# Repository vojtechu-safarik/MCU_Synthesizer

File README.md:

# Polyphonic Synthesizer for Teensy 4.1 

### Abstract
This project is an advanced realization of bachelor's project at Brno Univesity of Technology. 
It creates a digital synthesizer using a microcontroller development board, encompassing code development and a prototype build (including PCBs).
The C++ code has been made in VS Code using PlatformIO and it utilises Teensy Audio Library. 
The scripts that generate wavetables (as a header file) have been made using Python.
Those header files have been further edited in order to lower the amount of anti-aliasing using a MATLAB script. 

[**Video demonstration of the Synthesizer**](https://youtu.be/89R-V2SBuqk)

## Synthesis controls

### Oscillators
The synthesizer features both Poly and Unison voice allocation modes. Sound generation relies on wavetables categorized into 6 distinct families: Saw, Square (featuring Pulse Width Modulation), Triangle, Sine, Instrument, and Voice. Users can select the waveform type using the `Wave` control and seamlessly interpolate between variations using the `Shape` parameter. In Poly mode, each note gets its own independent audio chain, while Unison mode stacks three parallel oscillators per note for a thicker sound. Additionally, a sub-oscillator can be introduced, transposing the primary frequency one or two octaves down.

### Filters
The signal chain utilizes two main filters. The primary is a 24 dB/oct resonant Low-Pass Filter based on the Huovilainen New Moog mathematical model, which is capable of self-oscillation. This is followed in series by a 12 dB/oct High-Pass Filter based on the State Variable Filter model. The Low-Pass Filter also includes a dedicated Keyboard Tracking feature, allowing the cutoff frequency to scale dynamically with the pitch of the note played.

### Envelopes
Each voice is equipped with two dedicated ADSR (Attack, Decay, Sustain, Release) envelopes, allowing stages up to 3 seconds in length. One envelope shapes the final amplitude of the signal, while the other modulates the Low-Pass Filter's cutoff frequency. The filter envelope also features an `Intensity` control, enabling users to finely scale or invert the depth of the modulation.

### LFO
The Low-Frequency Oscillator can modulate the LPF Cutoff, Oscillator Shape, and Voice Pitch (Detune). It features four operational modes: `Free` (a single global LFO for all voices), `Retrig` (independent LFO per voice), and `Rise` or `Fall` (one-shot linear modulations triggered per note). Available waveforms include Sine, Saw Rise, Saw Fall, Square, and a randomized Noise sample. Users can adjust the modulation `Rate` (0.1–25 Hz), `Depth`, and a fade-in `Delay` of up to 3 seconds.

### Portamento
Available exclusively in Unison mode, Portamento introduces a smooth glide between overlapping notes. Its speed is synchronized to the global BPM and can be operated in two modes: `Time`, where the glide duration is a fixed note division regardless of the pitch distance, and `Rate`, where the glide duration scales with the interval, defined by the time it takes to travel one octave.

### Sequencer
A built-in step sequencer synchronizes to the global BPM and features two main performance modes. `Arp` mode functions as a traditional arpeggiator playing held notes in sequence, whereas `Latch` mode captures pressed keys into a buffer and plays them continuously without requiring the keys to be held. The sequence playback can be customized with order settings (Up, Down, As Played), octave duplications (+1 or +2 octaves), and an adjustable `Gate` parameter defining the note length (1–100%) per step. There's also an option to adjust the each individual step length via secret settings.

### Drone
This alternative ambient mode leverages 10 additional parallel oscillator chains utilizing simplified SVF filters, split into two alternating groups (A and B), alongside independent noise generators. Using the `Save` mode, users can capture the exact parameter settings of currently active voices and store them to one of 8 dedicated buttons. Switching to `Hold` mode allows users to endlessly play back these captured static drones concurrently with the standard synthesis engine.

## List of hardware components

* Teensy 4.1 Development board

* Audio Adaptor Board for Teensy (Rev D)

* 16-Channel Analog/Digital Multiplexer/Demultiplexer, CD74HC4067
  - used for various parameter configuration via potentiometers and toggle switches
  - 3 modules used in total 

  ### Mux 1 Channels:
  | Mux Channel | Parameter name | Connected Component |
  | :--- | :--- | :--- |
  | C0 | **Wave 1** | **Potentiometer** |
  | C1 | **Wave 2** | **Potentiometer** |
  | C2 | **Wave 3** | **Potentiometer** |
  | C3 | **Shape 1** | **Potentiometer** |
  | C4 | **Shape 2** | **Potentiometer** |
  | C5 | **Shape 3** | **Potentiometer** |
  | C6 | **Volume 1** | **Potentiometer** |
  | C7 | **Volume 2** | **Potentiometer** |
  | C8 | **Volume 3** | **Potentiometer** |
  | C9 | **Tune 1** | **Potentiometer** |
  | C10 | **Tune 2** | **Potentiometer** |
  | C11 | **Tune 3** | **Potentiometer** |
  | C12 | **Pink Noise** | **Potentiometer** |
  | C13 | **SynthMode - Poly** | **2-way Toggle Switch** |
  | C14 | **Sub-OSC - OFF** | **3-way Toggle Switch** |
  | C15 | **Sub-OSC - +2 octaves** | **3-way Toggle Switch** |

  ### Mux 2 Channels:
  | Mux Channel | Parameter name | Connected Component |
  | :--- | :--- | :--- |
  | C0 | **LPF Cutoff** | **Potentiometer** |
  | C1 | **LPF Resonance** | **Potentiometer** |
  | C2 | **Keyboard Tracking** | **Potentiometer** |
  | C3 | **Filter Envelope Intensity** | **Potentiometer** |
  | C4 | **HPF Cutoff** | **Potentiometer** |
  | C5 | **Filter Attack** | **Potentiometer** |
  | C6 | **Filter Decay** | **Potentiometer** |
  | C7 | **Filter Sustain** | **Potentiometer** |
  | C8 | **Filter Release** | **Potentiometer** |
  | C9 | **LFO Rate** | **Potentiometer** |
  | C10 | **LFO Depth** | **Potentiometer** |
  | C11 | **LFO Delay** | **Potentiometer** |
  | C12 | **Amplitude Attack** | **Potentiometer** |
  | C13 | **Amplitude Decay** | **Potentiometer** |
  | C14 | **Amplitude Sustain** | **Potentiometer** |
  | C15 | **Amplitude Release** | **Potentiometer** |

  ### Mux 3 Channels:
  | Mux Channel | Parameter name | Connected Component |
  | :--- | :--- | :--- |
  | C0 | **Master Volume** | **Potentiometer** |
  | C1 | **Sequencer Gate** | **Potentiometer** |
  | C2 | **LFO Type - Frequency** | **3-way Toggle Switch** |
  | C3 | **LFO Type - Tune** | **3-way Toggle Switch** |
  | C4 | **Portamento - ON** | **2-way Toggle Switch** |
  | C5 | **Portamento - Mode** | **2-way Toggle Switch** |
  | C6 | **Drone - mode** | **2-way Toggle Switch** |
  | C7 | **Sequencer Mode - OFF** | **3-way Toggle Switch** |
  | C8 | **Sequencer Mode - Latch** | **3-way Toggle Switch** |
  | C9 | **Sequencer Order - Up** | **3-way Toggle Switch** |
  | C10 | **Sequencer Order - Queue** | **3-way Toggle Switch** |
  | C11 | **Sequencer Octaves - 0** | **3-way Toggle Switch** |
  | C12 | **Sequencer Octaves - 2** | **3-way Toggle Switch** |

* 8-bit I/O Expander I2C-Bus, PCF8574T
  - used for LED signals for parameter state identification 
  - 2 modules used in total 

  ### I/O Expander 1 Pinout:
  | I/O Expander Pin | Parameter name |
  | :--- | :--- |
  | P0 | **LFO Mode #1** |
  | P1 | **LFO Mode #2** |
  | P2 | **LFO Mode #3** |
  | P3 | **LFO Mode #4** |
  | P4 | **LFO Wave #1** |
  | P5 | **LFO Wave #2** |
  | P6 | **LFO Wave #3** |
  | P7 | **LFO Wave #4** |

  ### I/O Expander 2 Pinout:
  | I/O Expander Pin | Parameter name |
  | :--- | :--- |
  | P0 | **Sequencer Rate #3** |
  | P1 | **Sequencer Rate #4** |
  | P2 | **LFO Wave #5** |
  | P3 | **Portamento Rate #1** |
  | P4 | **Portamento Rate #2** |
  | P5 | **Portamento Rate #3** |
  | P6 | **Portamento Rate #4** |
  | P7 | **Portamento Rate #5** |

* 3.2" 240x320 TFT display, ILI9341
  - SPI Display used for wavetable state reading

* Potentiometers
  - 20 Rotary B5K (WH148)
  - 11 Slider B10K (60mm)

* Rotary Encoder, KY-040
  - used for BPM configuration
  - button is used for preset selection

* Keyboard switches, MX linear Red
  - set up as a matrix to preserve pins

* Toggle switches
- 3× KN3 2-way toggle switch
- 2× KN3 3-way toggle switch
- 1× MTS-102 2-way toggle switch
- 3× MTS-103 3-way toggle switch

* Basic electronic components
- Resistors
  - 1× 100 (for Display backlight)
  - 22× 1k (for LEDs)
  - 14× 10k (pull resistors)
- Capacitors
  - 5× Ceramic 100nF (for coupling)
- Diodes
  - 43× 1N4148 (for Keyboard switches)
- LEDs
  - 22× 3mm Red
- Terminal blocks
  - 45× 3-Pin 2.54mm
  - 6× 2-Pin 2.54mm

## Circuit & PCB schematics

Circuit & PCB schematics have been made in KiCad 9.0 and the project is available [here.](./Design/KiCad)

## Pinout Configuration

| Teensy Pin | Pin name | Connected Components |
| :--- | :--- | :--- |
| 0 | **SW** | **Rotary Encoder** |
| 1 | **DT** | **Rotary Encoder** |
| 2 | **CLK** | **Rotary Encoder** |
| 3 | **S0** | **Mux #1, #2 and #3** |
| 4 | **S1** | **Mux #1, #2 and #3** |
| 5 | **S2** | **Mux #1, #2 and #3** |
| 6 | **S3** | **Mux #1, #2 and #3** |
| 7 | **DIN** | **Audioshield** |
| 8 | **DOUT** | **Audioshield** |
| 9 | **D/C** | **Display** |
| 10 | **CS** | **Display** |
| 11 | **SDI (MOSI)** | **Display** |
| 12 | **SDO (MISO)** | **Display** |
| 13 | **SCK** | **Display** |
| 14 | **Signal #1** | **LED #1 (Sequencer Rate #1)** |
| 15 | **Signal #2** | **LED #2 (Octave #4)** |
| 16 | **Signal #3** | **LED #3 (Octave #3)** |
| 17 | **Signal #4** | **LED #4 (Octave #2)** |
| 18 | **SDA** | **Audioshield** |
| 19 | **SCL** | **Audioshield** |
| 20 | **LRCLK** | **Audioshield** |
| 21 | **BCLK** | **Audioshield** |
| 22 | **Signal #5** | **LED #5 (Octave #1)** |
| 23 | **MCLK** | **Audioshield** |
| 24 | **Row #1** | **Keyboard** |
| 25 | **Row #2** | **Keyboard** |
| 26 | **Row #3** | **Keyboard** |
| 27 | **Row #4** | **Keyboard** |
| 28 | **Row #5** | **Keyboard** |
| 29 | **Row #6** | **Keyboard** |
| 30 | **Row #7** | **Keyboard** |
| 31 | **Row #8** | **Keyboard** |
| 32 | **Row #9** | **Keyboard** |
| 33 | **Column #1** | **Keyboard** |
| 34 | **Column #2** | **Keyboard** |
| 35 | **Column #3** | **Keyboard** |
| 36 | **Column #4** | **Keyboard** |
| 37 | **Column #5** | **Keyboard** |
| 38 | **Signal #6** | **LED #6 (Sequencer Rate #2)** |
| 39 | **Sig (A15)** | **Mux #1** |
| 40 | **Sig (A16)** | **Mux #2** |
| 41 | **Sig (A17)** | **Mux #3** |

### Images

### 3D Model

The 3D model has been made for laser engraving of the control panel. 

### Possible improvements

* The Line Out connector doesn't work now, and I don't know why, but I suppose it's not of mechanical nature.
* The GND is pretty noisy as of now, especially when powering via USB.
* Preset function isn't developed yet, but will be once I return to this project later.

## References

* Teensy 4.1 information: [link PJRC.com](https://www.pjrc.com/store/teensy41.html)
* Audio Adaptor Board for Teensy information: [link PJRC.com](https://www.pjrc.com/store/teensy3_audio.html)
* Incredible source of information and amazing YouTube content: [link notesandvolts.com](https://www.notesandvolts.com)
* I hereby acknowledge use of free-license AI tool for coding: [link gemini.google.com](https://gemini.google.com)

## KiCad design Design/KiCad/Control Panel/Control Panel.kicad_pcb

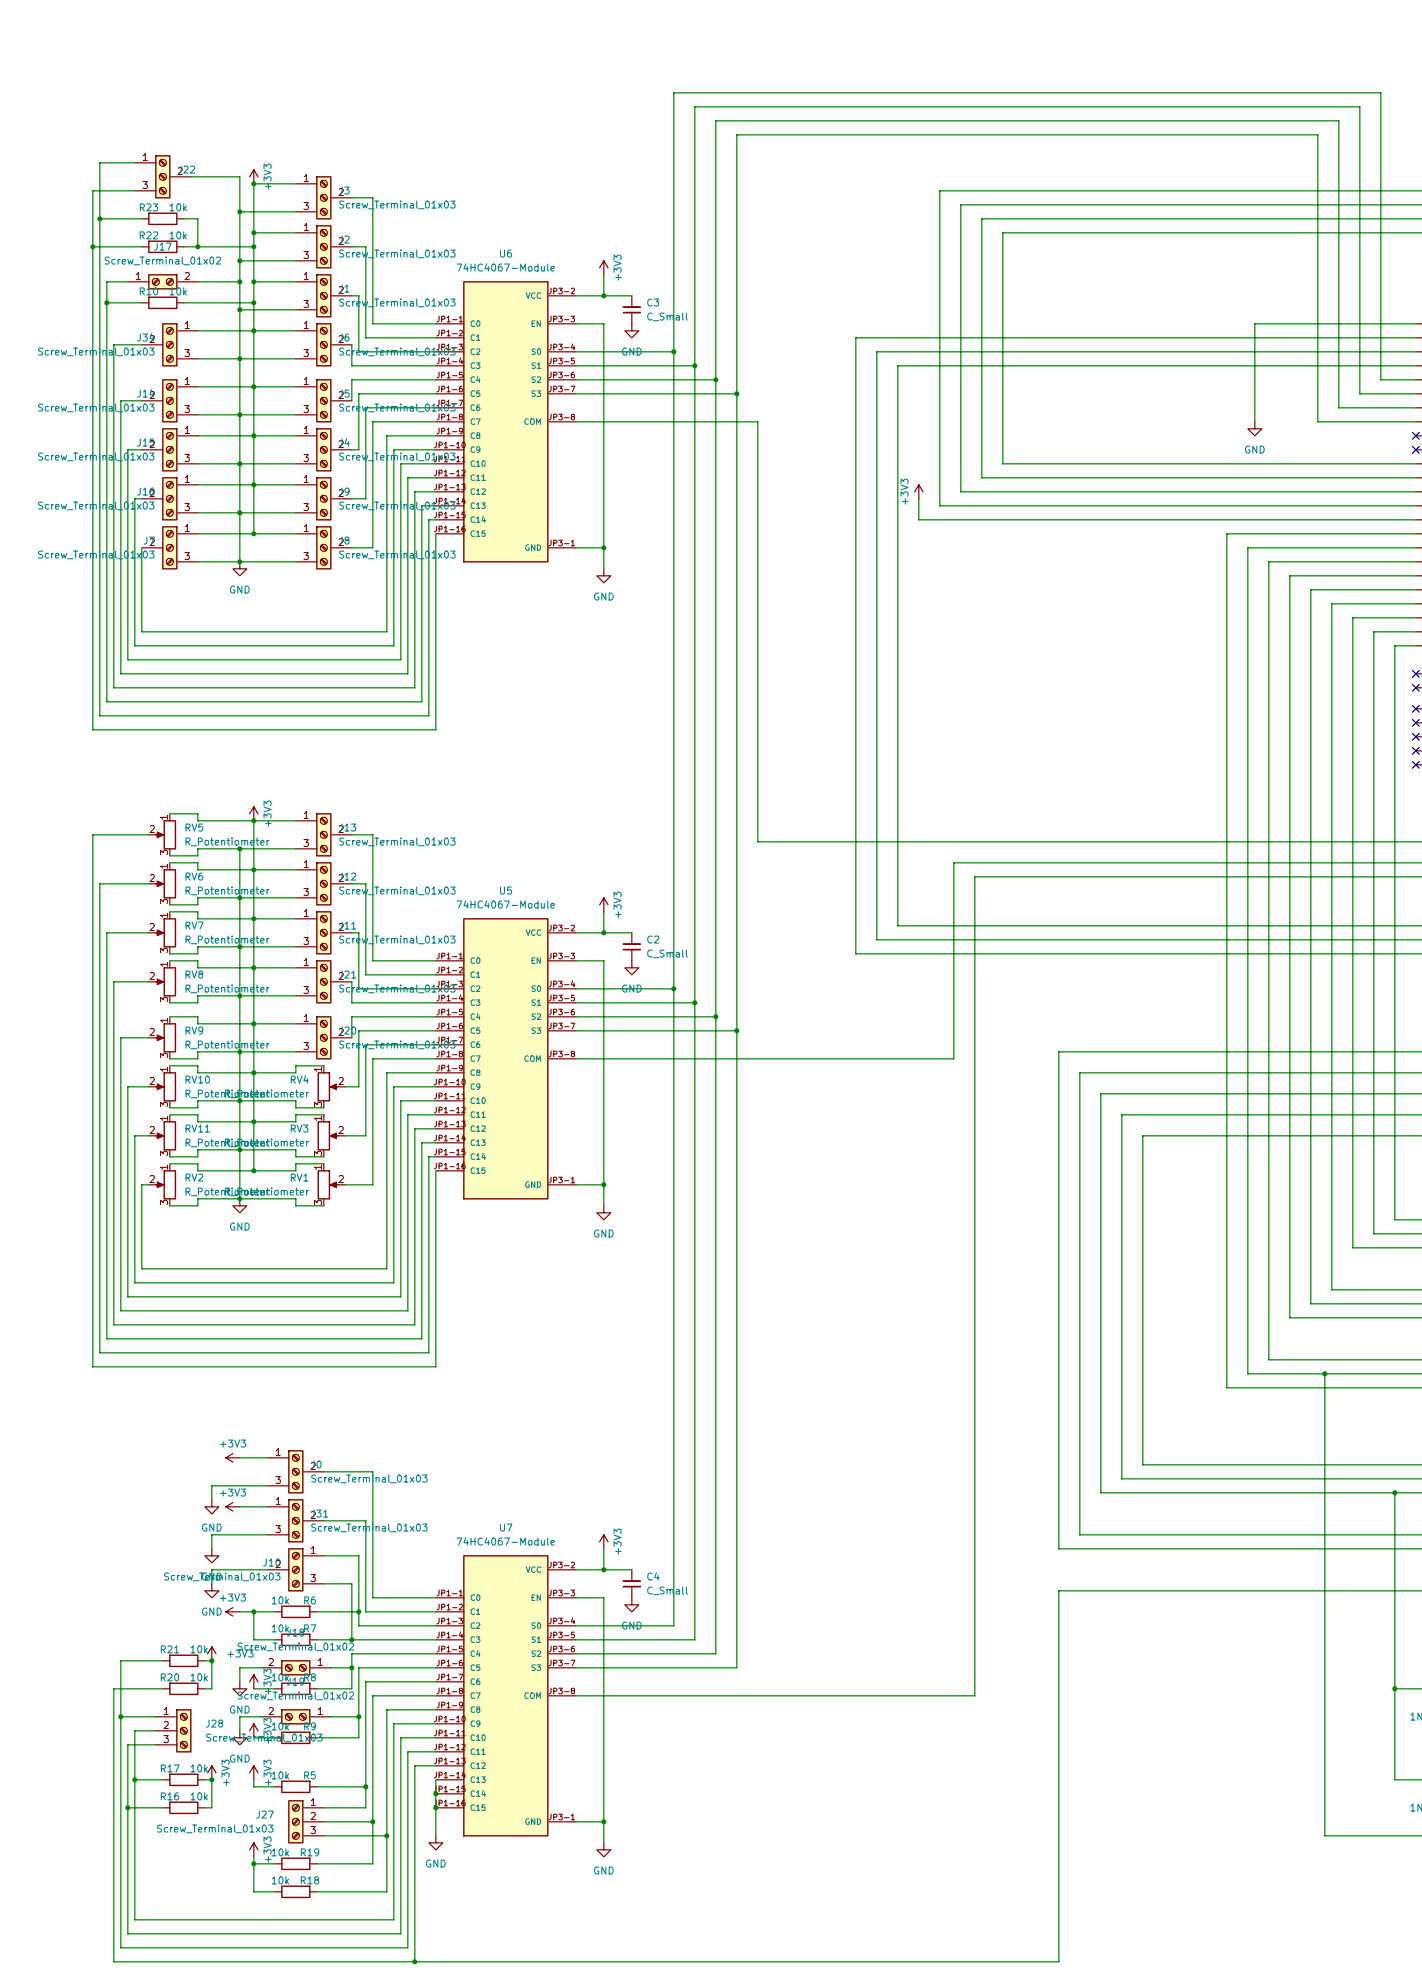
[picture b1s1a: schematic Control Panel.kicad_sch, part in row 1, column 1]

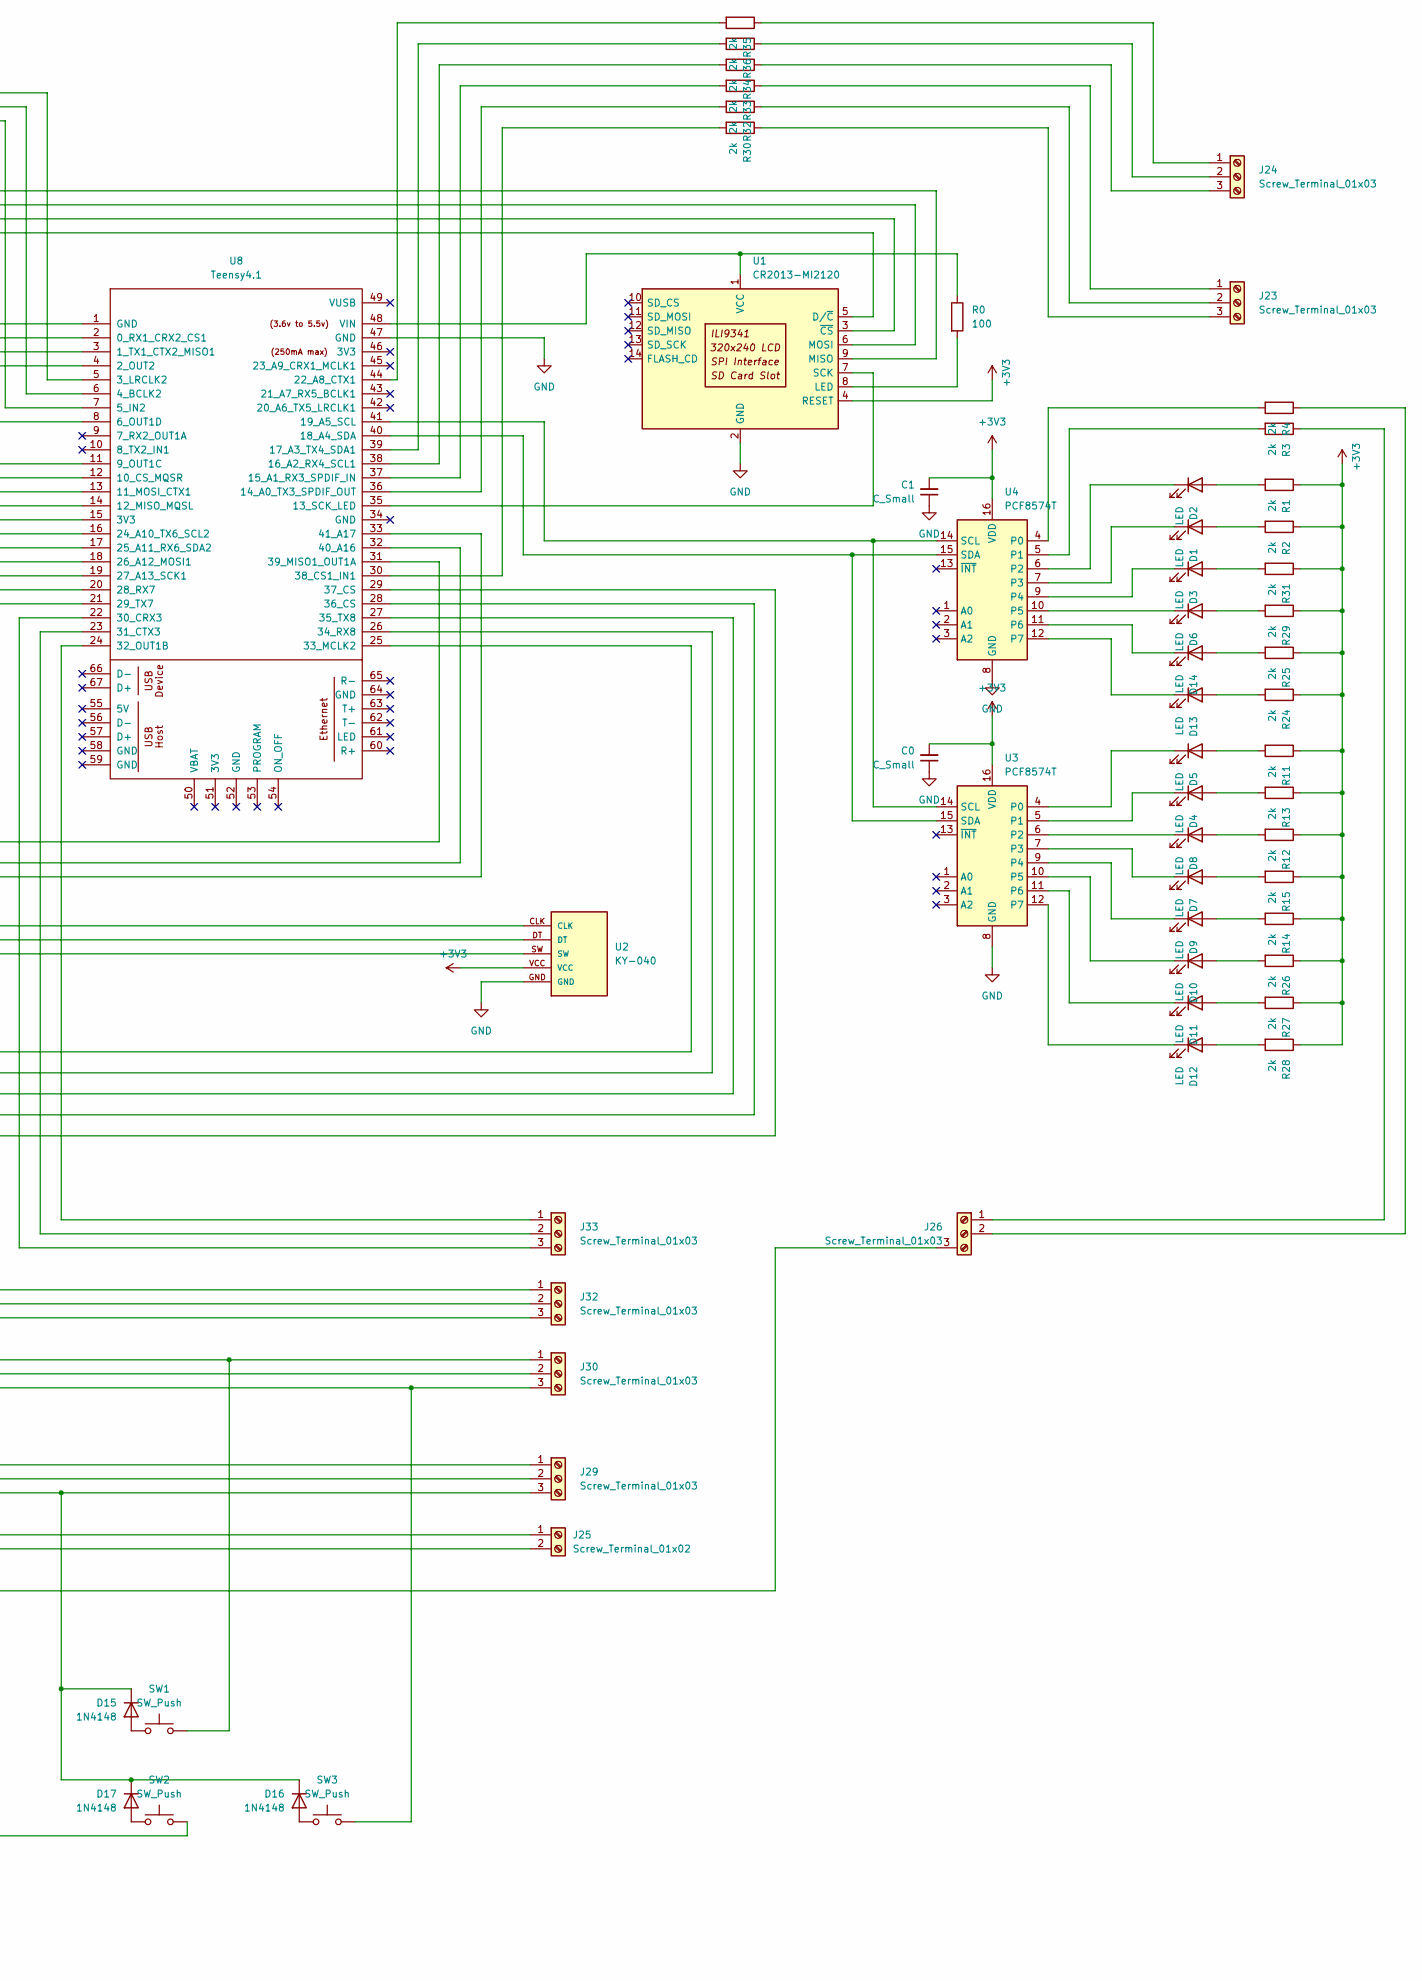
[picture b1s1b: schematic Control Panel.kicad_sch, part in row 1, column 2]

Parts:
C0, C1, C2, C3, C4: C_Small; C_Disc_D5.0mm_W2.5mm_P2.50mm
D1, D2, D3, D4, D5, D6, D7, D8, D9, D10, D11, D12, D13, D14: LED; LED_D3.0mm_Clear
D15, D16, D17: 1N4148; D_DO-35_SOD27_P7.62mm_Horizontal
J0, J1, J2, J3, J4, J5, J6, J7, J8, J9, J10, J11, J12, J13, J14, J15, J16, J20, J21, J22, J23, J24, J26, J27, J28, J29, J30, J31, J32, J33, J34: Screw_Terminal_01x03; TerminalBlock_Xinya_XY308-2.54-3P_1x03_P2.54mm_Horizontal
J17, J18, J19, J25: Screw_Terminal_01x02; TerminalBlock_Xinya_XY308-2.54-2P_1x02_P2.54mm_Horizontal
R0: 100; R_Axial_DIN0207_L6.3mm_D2.5mm_P7.62mm_Horizontal
R1, R2, R3, R4, R11, R12, R13, R14, R15, R24, R25, R26, R27, R28, R29, R30, R31, R32, R33, R34, R35, R36: 2k; R_Axial_DIN0207_L6.3mm_D2.5mm_P7.62mm_Horizontal
R5, R6, R7, R8, R9, R10, R16, R17, R18, R19, R20, R21, R22, R23: 10k; R_Axial_DIN0207_L6.3mm_D2.5mm_P7.62mm_Horizontal
RV1, RV2, RV3, RV4, RV5, RV6, RV7, RV8, RV9, RV10, RV11: R_Potentiometer; Potentiometer_Bourns_PTA4543_Single_Slide
SW1, SW2, SW3: SW_Push; SW_Cherry_MX_1.00u_Plate
U1: CR2013-MI2120; ILI9341_3p2_320x240
U2: KY-040; KY-040-PORT
U3, U4: PCF8574T; PCF8574T_Custom
U5, U6, U7: 74HC4067-Module; MODULE-74HC4067; PARTREV v11
U8: Teensy4.1; Teensy41

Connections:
+3V3: C0.2, C1.2, C2.2, C3.2, C4.2, J0.1, J1.1, J2.1, J3.1, J4.1, J5.1, J6.1, J7.1, J8.1, J9.1, J11.1, J12.1, J13.1, J14.1, J15.1, J16.1, J20.1, J21.1, J31.1, J34.1, R1.1, R2.1, R5.1, R6.1, R7.1, R8.1, R9.1, R10.1, R11.1, R12.1, R13.1, R14.1, R15.1, R16.1, R17.1, R18.1, R19.1, R20.1, R21.1, R22.1, R23.1, R24.1, R25.1, R26.1, R27.1, R28.1, R29.1, R31.1, RV1.1, RV2.1, RV3.1, RV4.1, RV5.1, RV6.1, RV7.1, RV8.1, RV9.1, RV10.1, RV11.1, U1.4 (RESET), U2.VCC, U3.16 (VDD), U4.16 (VDD), U5.JP3-2 (VCC), U6.JP3-2 (VCC), U7.JP3-2 (VCC), U8.15 (3V3)
GND: C0.1, C1.1, C2.1, C3.1, C4.1, J0.3, J1.3, J2.3, J3.3, J4.3, J5.3, J6.3, J7.3, J8.3, J9.3, J10.2, J11.3, J12.3, J13.3, J14.3, J15.3, J16.3, J17.2, J18.2, J19.2, J20.3, J21.3, J22.2, J31.3, J34.3, RV1.3, RV2.3, RV3.3, RV4.3, RV5.3, RV6.3, RV7.3, RV8.3, RV9.3, RV10.3, RV11.3, U1.2 (GND), U2.GND, U3.8 (GND), U4.8 (GND), U5.JP3-1 (GND), U5.JP3-3 (EN), U6.JP3-1 (GND), U6.JP3-3 (EN), U7.JP1-14 (C13), U7.JP1-15 (C14), U7.JP1-16 (C15), U7.JP3-1 (GND), U7.JP3-3 (EN), U8.1 (GND), U8.47 (GND)
unnamed: D1.2 (A), R2.2
unnamed: D1.1 (K), U4.7 (P3)
unnamed: D2.2 (A), R1.2
unnamed: D2.1 (K), U4.6 (P2)
unnamed: D3.2 (A), R31.2
unnamed: D3.1 (K), U4.9 (P4)
unnamed: D4.2 (A), R13.2
unnamed: D4.1 (K), U3.5 (P1)
unnamed: D5.2 (A), R11.2
unnamed: D5.1 (K), U3.4 (P0)
unnamed: D6.2 (A), R29.2
unnamed: D6.1 (K), U4.10 (P5)
unnamed: D7.2 (A), R15.2
unnamed: D7.1 (K), U3.7 (P3)
unnamed: D8.2 (A), R12.2
unnamed: D8.1 (K), U3.6 (P2)
unnamed: D9.2 (A), R14.2
unnamed: D9.1 (K), U3.9 (P4)
unnamed: D10.2 (A), R26.2
unnamed: D10.1 (K), U3.10 (P5)
unnamed: D11.2 (A), R27.2
unnamed: D11.1 (K), U3.11 (P6)
unnamed: D12.2 (A), R28.2
unnamed: D12.1 (K), U3.12 (P7)
unnamed: D13.2 (A), R24.2
unnamed: D13.1 (K), U4.12 (P7)
unnamed: D14.2 (A), R25.2
unnamed: D14.1 (K), U4.11 (P6)
unnamed: D15.2 (A), SW1.2
unnamed: D15.1 (K), D16.1 (K), D17.1 (K), J29.3, U8.27 (35_TX8)
unnamed: D16.2 (A), SW3.2
unnamed: D17.2 (A), SW2.2
unnamed: J0.2, U7.JP1-1 (C0)
unnamed: J1.2, U6.JP1-3 (C2)
unnamed: J2.2, U6.JP1-2 (C1)
unnamed: J3.2, U6.JP1-1 (C0)
unnamed: J4.2, U6.JP1-6 (C5)
unnamed: J5.2, U6.JP1-5 (C4)
unnamed: J6.2, U6.JP1-4 (C3)
unnamed: J7.2, U6.JP1-9 (C8)
unnamed: J8.2, U6.JP1-8 (C7)
unnamed: J9.2, U6.JP1-7 (C6)
unnamed: J10.1, R6.2, U7.JP1-3 (C2)
unnamed: J10.3, R7.2, U7.JP1-4 (C3)
unnamed: J11.2, U5.JP1-3 (C2)
unnamed: J12.2, U5.JP1-2 (C1)
unnamed: J13.2, U5.JP1-1 (C0)
unnamed: J14.2, U6.JP1-12 (C11)
unnamed: J15.2, U6.JP1-11 (C10)
unnamed: J16.2, U6.JP1-10 (C9)
unnamed: J17.1, R10.2, U6.JP1-14 (C13)
unnamed: J18.1, R8.2, U7.JP1-5 (C4)
unnamed: J19.1, R9.2, U7.JP1-6 (C5)
unnamed: J20.2, U5.JP1-5 (C4)
unnamed: J21.2, U5.JP1-4 (C3)
unnamed: J22.1, R23.2, U6.JP1-15 (C14)
unnamed: J22.3, R22.2, U6.JP1-16 (C15)
unnamed: J23.1, R33.1
unnamed: J23.2, R32.1
unnamed: J23.3, R30.1
unnamed: J24.1, R35.1
unnamed: J24.2, R36.1
unnamed: J24.3, R34.1
unnamed: J25.1, U8.26 (34_RX8)
unnamed: J25.2, U8.25 (33_MCLK2)
unnamed: J26.1, R3.1
unnamed: J26.2, R4.1
unnamed: J26.3, R20.2, U7.JP1-13 (C12)
unnamed: J27.1, R5.2, U7.JP1-7 (C6)
unnamed: J27.2, R19.2, U7.JP1-8 (C7)
unnamed: J27.3, R18.2, U7.JP1-9 (C8)
unnamed: J28.1, R21.2, U7.JP1-12 (C11)
unnamed: J28.2, R17.2, U7.JP1-10 (C9)
unnamed: J28.3, R16.2, U7.JP1-11 (C10)
unnamed: J29.1, U8.29 (37_CS)
unnamed: J29.2, U8.28 (36_CS)
unnamed: J30.1, SW1.1, U8.18 (26_A12_MOSI1)
unnamed: J30.2, SW2.1, U8.17 (25_A11_RX6_SDA2)
unnamed: J30.3, SW3.1, U8.16 (24_A10_TX6_SCL2)
unnamed: J31.2, U7.JP1-2 (C1)
unnamed: J32.1, U8.21 (29_TX7)
unnamed: J32.2, U8.20 (28_RX7)
unnamed: J32.3, U8.19 (27_A13_SCK1)
unnamed: J33.1, U8.24 (32_OUT1B)
unnamed: J33.2, U8.23 (31_CTX3)
unnamed: J33.3, U8.22 (30_CRX3)
unnamed: J34.2, U6.JP1-13 (C12)
unnamed: U1.5 (D/~C), U8.11 (9_OUT1C)
unnamed: R0.2, U1.8 (LED)
unnamed: U1.9 (MISO), U8.14 (12_MISO_MQSL)
unnamed: U1.6 (MOSI), U8.13 (11_MOSI_CTX1)
unnamed: U1.7 (SCK), U8.35 (13_SCK_LED)
unnamed: R0.1, U1.1 (VCC), U8.48 (VIN)
unnamed: U1.3 (~CS), U8.12 (10_CS_MQSR)
unnamed: U3.14 (SCL), U4.14 (SCL), U8.41 (19_A5_SCL)
unnamed: U3.15 (SDA), U4.15 (SDA), U8.40 (18_A4_SDA)
unnamed: R4.2, U4.4 (P0)
unnamed: R3.2, U4.5 (P1)
unnamed: RV4.2, U5.JP1-6 (C5)
unnamed: RV3.2, U5.JP1-7 (C6)
unnamed: RV1.2, U5.JP1-8 (C7)
unnamed: RV2.2, U5.JP1-9 (C8)
unnamed: RV11.2, U5.JP1-10 (C9)
unnamed: RV10.2, U5.JP1-11 (C10)
unnamed: RV9.2, U5.JP1-12 (C11)
unnamed: RV8.2, U5.JP1-13 (C12)
unnamed: RV7.2, U5.JP1-14 (C13)
unnamed: RV6.2, U5.JP1-15 (C14)
unnamed: RV5.2, U5.JP1-16 (C15)
unnamed: U5.JP3-8 (COM), U8.32 (40_A16)
unnamed: U5.JP3-4 (S0), U6.JP3-4 (S0), U7.JP3-4 (S0), U8.5 (3_LRCLK2)
unnamed: U5.JP3-5 (S1), U6.JP3-5 (S1), U7.JP3-5 (S1), U8.6 (4_BCLK2)
unnamed: U5.JP3-6 (S2), U6.JP3-6 (S2), U7.JP3-6 (S2), U8.7 (5_IN2)
unnamed: U5.JP3-7 (S3), U6.JP3-7 (S3), U7.JP3-7 (S3), U8.8 (6_OUT1D)
unnamed: U6.JP3-8 (COM), U8.31 (39_MISO1_OUT1A)
unnamed: U7.JP3-8 (COM), U8.33 (41_A17)
unnamed: U2.SW, U8.2 (0_RX1_CRX2_CS1)
unnamed: U2.DT, U8.3 (1_TX1_CTX2_MISO1)
unnamed: U2.CLK, U8.4 (2_OUT2)
unnamed: R32.2, U8.36 (14_A0_TX3_SPDIF_OUT)
unnamed: R33.2, U8.37 (15_A1_RX3_SPDIF_IN)
unnamed: R34.2, U8.38 (16_A2_RX4_SCL1)
unnamed: R36.2, U8.39 (17_A3_TX4_SDA1)
unnamed: R35.2, U8.44 (22_A8_CTX1)
unnamed: R30.2, U8.30 (38_CS1_IN1)

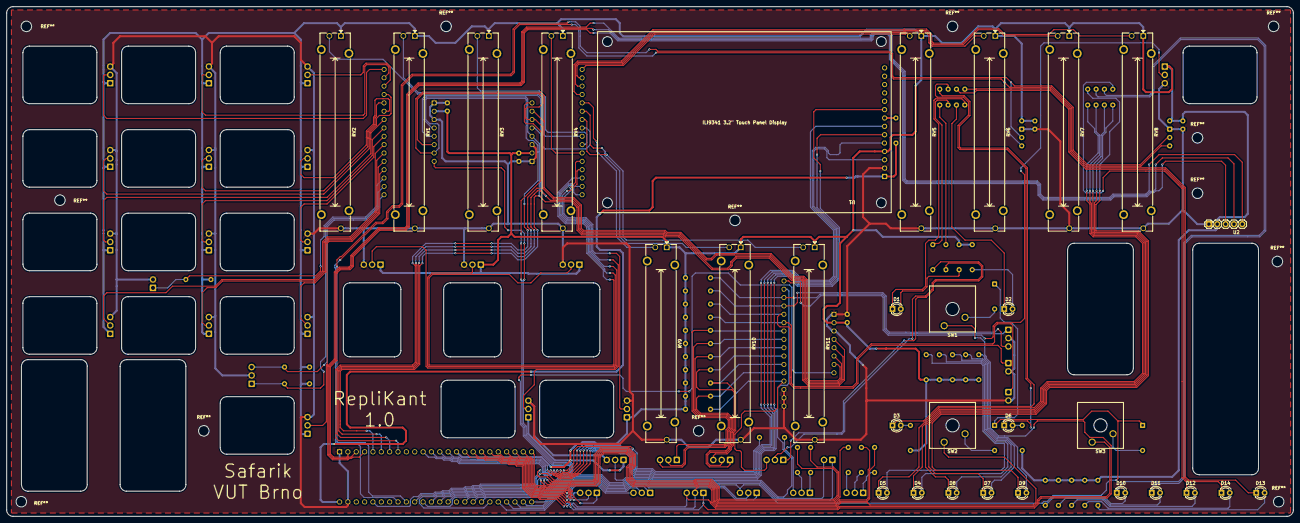
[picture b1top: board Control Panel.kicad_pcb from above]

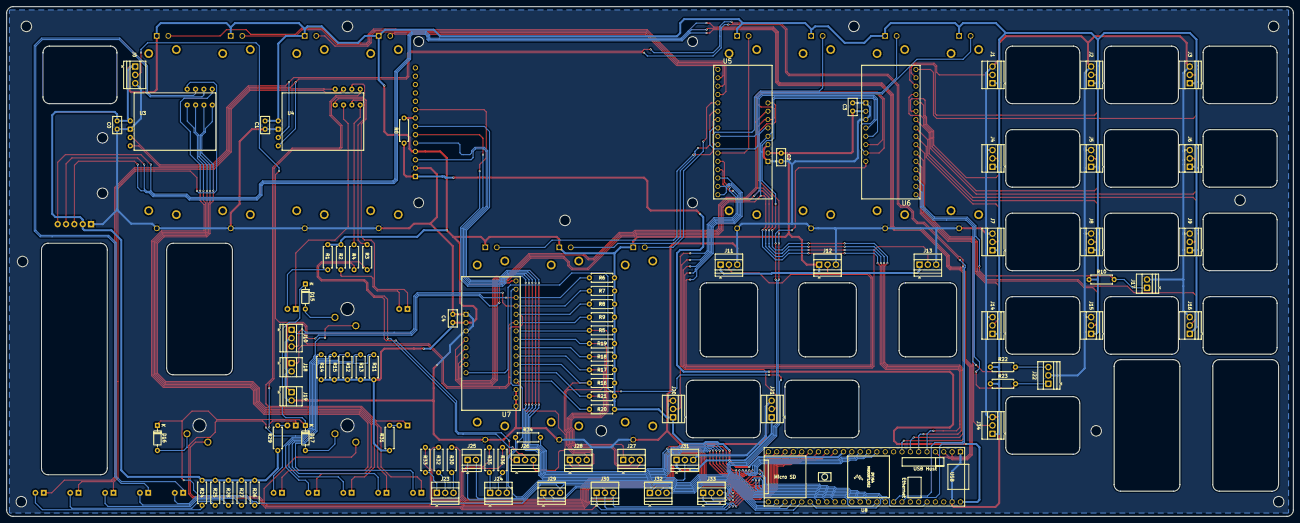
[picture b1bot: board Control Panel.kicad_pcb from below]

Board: 2 copper layers, 391.3 x 155.0 mm, 116 parts (86 on the bottom side), 127 nets.

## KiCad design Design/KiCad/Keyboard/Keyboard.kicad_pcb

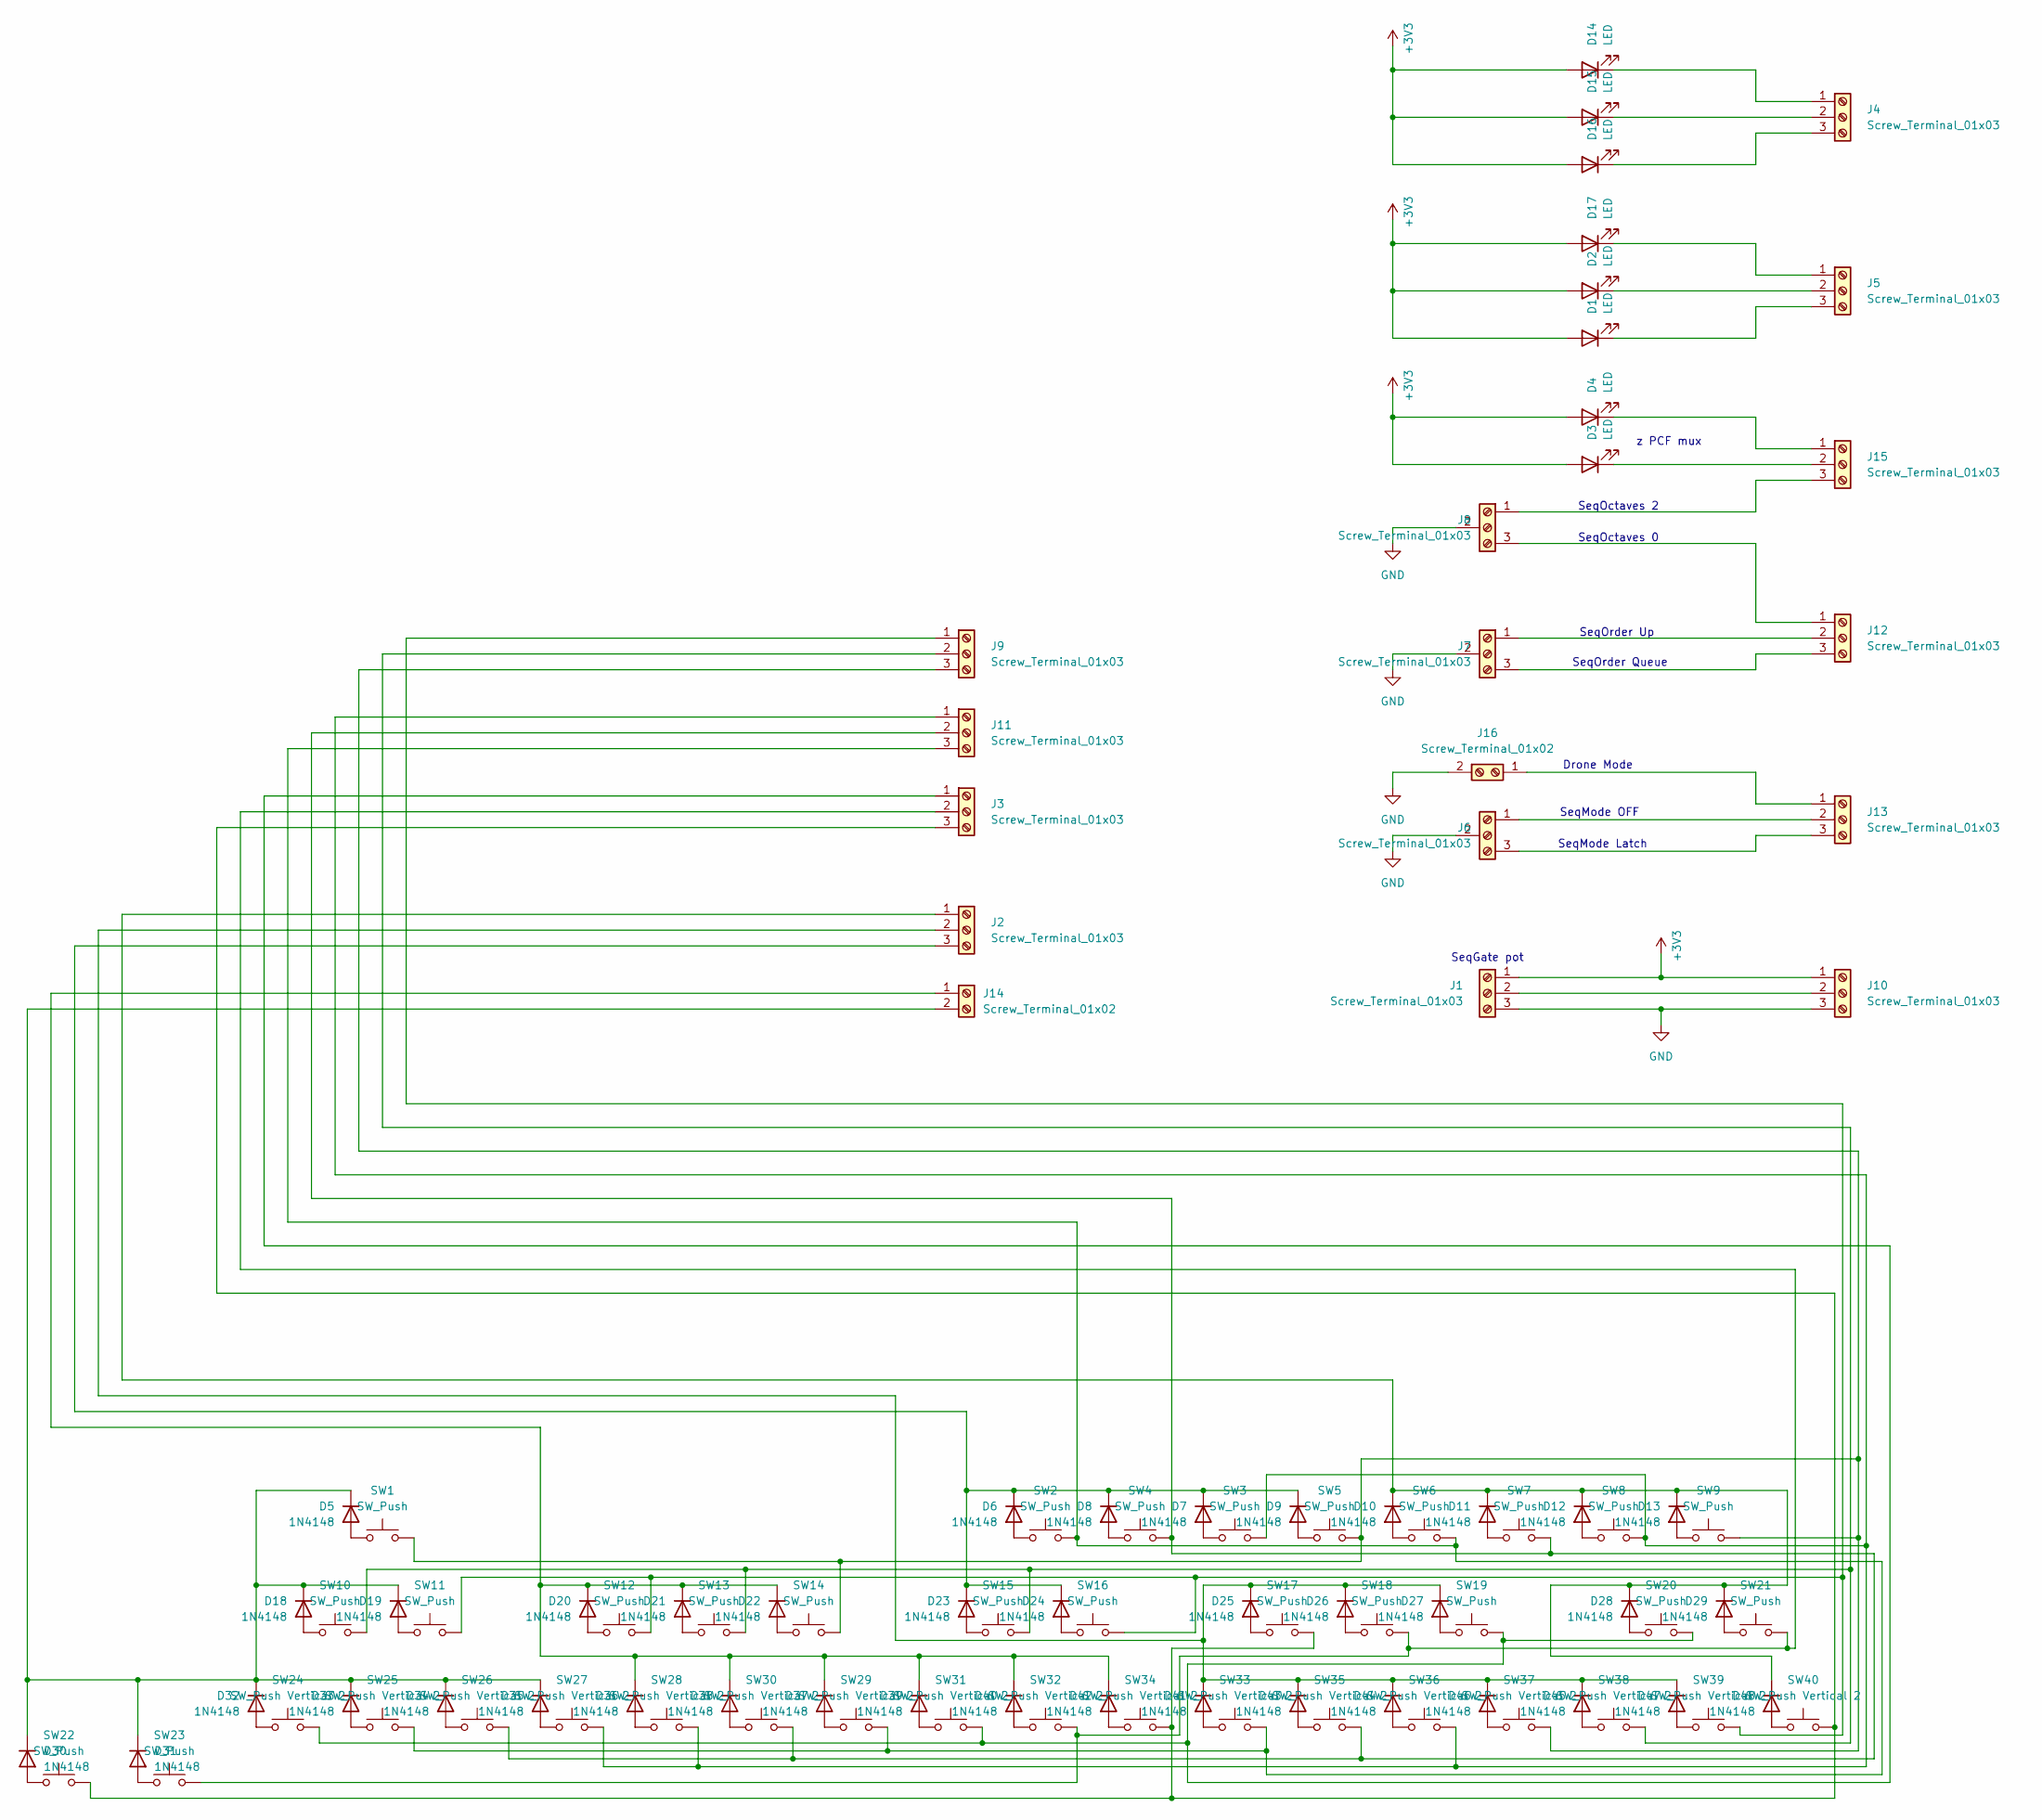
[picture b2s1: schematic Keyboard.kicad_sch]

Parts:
D1, D2, D3, D4, D14, D15, D16, D17: LED; LED_D3.0mm_Clear
D5, D6, D7, D8, D9, D10, D11, D12, D13, D18, D19, D20, D21, D22, D23, D24, D25, D26, D27, D28, D29, D30, D31, D32, D33, D34, D35, D36, D37, D38, D39, D40, D41, D42, D43, D44, D45, D46, D47, D48: 1N4148; D_DO-35_SOD27_P7.62mm_Horizontal
J1, J2, J3, J4, J5, J6, J7, J8, J9, J10, J11, J12, J13, J15: Screw_Terminal_01x03; TerminalBlock_Xinya_XY308-2.54-3P_1x03_P2.54mm_Horizontal
J14, J16: Screw_Terminal_01x02; TerminalBlock_Xinya_XY308-2.54-2P_1x02_P2.54mm_Horizontal
SW1, SW2, SW3, SW4, SW5, SW6, SW7, SW8, SW9, SW10, SW11, SW12, SW13, SW14, SW15, SW16, SW17, SW18, SW19, SW20, SW21, SW22, SW23: SW_Push; SW_Cherry_MX_1.00u_Plate
SW24, SW25, SW26, SW27, SW28, SW29, SW30, SW31, SW32, SW33, SW34, SW35, SW36, SW37, SW38, SW39, SW40: SW_Push Vertical 2; SW_Cherry_MX_2.00u_Vertical_Plate

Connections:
+3V3: D1.2 (A), D2.2 (A), D3.2 (A), D4.2 (A), D14.2 (A), D15.2 (A), D16.2 (A), D17.2 (A), J1.1, J10.1
GND: J1.3, J6.2, J7.2, J8.2, J10.3, J16.2
unnamed: D1.1 (K), J5.3
unnamed: D2.1 (K), J5.2
unnamed: D3.1 (K), J15.2
unnamed: D4.1 (K), J15.1
unnamed: D5.2 (A), SW1.2
unnamed: D6.2 (A), SW2.2
unnamed: D7.2 (A), SW3.2
unnamed: D8.2 (A), SW4.2
unnamed: D9.2 (A), SW5.2
unnamed: D10.2 (A), SW6.2
unnamed: D10.1 (K), D11.1 (K), D12.1 (K), D13.1 (K), D28.1 (K), D29.1 (K), D48.1 (K), J2.1
unnamed: D11.2 (A), SW7.2
unnamed: D12.2 (A), SW8.2
unnamed: D13.2 (A), SW9.2
unnamed: D14.1 (K), J4.1
unnamed: D15.1 (K), J4.2
unnamed: D16.1 (K), J4.3
unnamed: D17.1 (K), J5.1
unnamed: D18.2 (A), SW10.2
unnamed: D5.1 (K), D18.1 (K), D19.1 (K), D30.1 (K), D31.1 (K), D32.1 (K), D33.1 (K), D34.1 (K), D35.1 (K), J14.2
unnamed: D19.2 (A), SW11.2
unnamed: D20.2 (A), SW12.2
unnamed: D20.1 (K), D21.1 (K), D22.1 (K), D36.1 (K), D37.1 (K), D38.1 (K), D39.1 (K), D40.1 (K), D42.1 (K), J14.1
unnamed: D21.2 (A), SW13.2
unnamed: D22.2 (A), SW14.2
unnamed: D23.2 (A), SW15.2
unnamed: D6.1 (K), D7.1 (K), D8.1 (K), D9.1 (K), D23.1 (K), D24.1 (K), J2.3
unnamed: D24.2 (A), SW16.2
unnamed: D25.2 (A), SW17.2
unnamed: D25.1 (K), D26.1 (K), D27.1 (K), D41.1 (K), D43.1 (K), D44.1 (K), D45.1 (K), D46.1 (K), D47.1 (K), J2.2
unnamed: D26.2 (A), SW18.2
unnamed: D27.2 (A), SW19.2
unnamed: D28.2 (A), SW20.2
unnamed: D29.2 (A), SW21.2
unnamed: D30.2 (A), SW22.2
unnamed: D31.2 (A), SW23.2
unnamed: D32.2 (A), SW24.2
unnamed: D33.2 (A), SW25.2
unnamed: D34.2 (A), SW26.2
unnamed: D35.2 (A), SW27.2
unnamed: D36.2 (A), SW28.2
unnamed: D37.2 (A), SW29.2
unnamed: D38.2 (A), SW30.2
unnamed: D39.2 (A), SW31.2
unnamed: D40.2 (A), SW32.2
unnamed: D41.2 (A), SW33.2
unnamed: D42.2 (A), SW34.2
unnamed: D43.2 (A), SW35.2
unnamed: D44.2 (A), SW36.2
unnamed: D45.2 (A), SW38.2
unnamed: D46.2 (A), SW37.2
unnamed: D47.2 (A), SW39.2
unnamed: D48.2 (A), SW40.2
unnamed: J1.2, J10.2
unnamed: J3.1, SW19.1, SW20.1, SW24.1, SW31.1
unnamed: J3.2, SW18.1, SW21.1, SW23.1, SW32.1
unnamed: J3.3, SW17.1, SW22.1, SW34.1, SW40.1
unnamed: J9.1, SW11.1, SW12.1, SW16.1, SW39.1
unnamed: J9.2, SW10.1, SW13.1, SW15.1, SW38.1
unnamed: J9.3, SW1.1, SW5.1, SW9.1, SW14.1, SW37.1
unnamed: J11.1, SW3.1, SW8.1, SW27.1, SW28.1, SW36.1
unnamed: J11.2, SW4.1, SW7.1, SW26.1, SW30.1, SW35.1
unnamed: J11.3, SW2.1, SW6.1, SW25.1, SW29.1, SW33.1
unnamed: J8.3, J12.1
unnamed: J7.1, J12.2
unnamed: J7.3, J12.3
unnamed: J13.1, J16.1
unnamed: J6.1, J13.2
unnamed: J6.3, J13.3
unnamed: J8.1, J15.3

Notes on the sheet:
SeqOctaves 2
Drone Mode
SeqOrder Queue
SeqGate pot
SeqOctaves 0
SeqOrder Up
SeqMode OFF
z PCF mux
SeqMode Latch

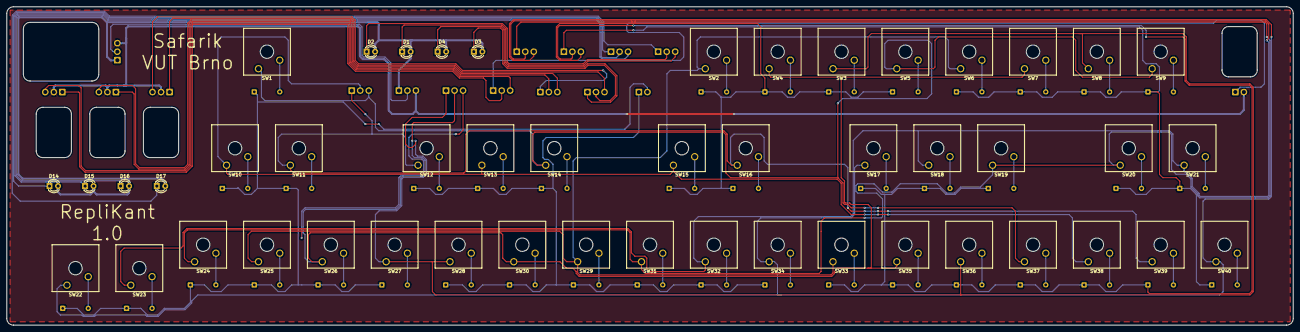
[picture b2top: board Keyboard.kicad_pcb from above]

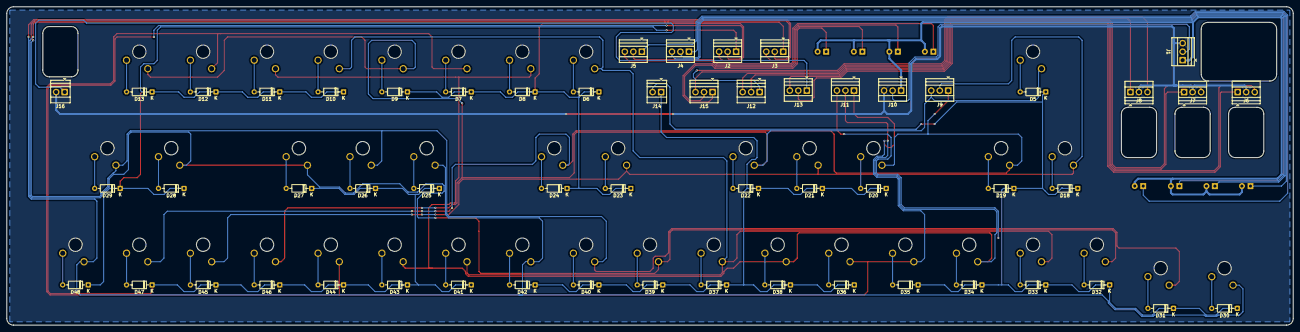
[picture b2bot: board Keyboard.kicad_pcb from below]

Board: 2 copper layers, 383.9 x 95.0 mm, 104 parts (56 on the bottom side), 72 nets.
